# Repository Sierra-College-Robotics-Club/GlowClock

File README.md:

# GlowClock

This is a project from Sierra College Robotics Club, A glow-in-the-dark display, activated by UV LEDs scanning over a glow-in-the-dark surface. It displays messages, the time, and features various patterns and simple games! 

See [The Schematic](GlowClockPCB/Docs/GlowClockSchematicPrint.pdf) and [The Code](code/glowClock.py) to get started working with it.

The GlowClock design evolved from our previous project, the Whiteboard Clock, but with the goals of being more mechanically reliable, while showing a new and unique way of using technology we're all familar with: Glow in the dark materials!

The GlowClock is a collaborative effort by the Robotics Club, featuring PCB design and software by Patrick Leiser, with mechanical design and assembly contributions from many talented club members.

## In the media
We presented the GlowClock at OpenSauce 2025, and were featured in [This Video](https://youtu.be/PQWQQJ_izac?t=115) by Jeff Geerling. We also posted some media on [our instagram](https://www.instagram.com/p/DJci4YWBg5E/)

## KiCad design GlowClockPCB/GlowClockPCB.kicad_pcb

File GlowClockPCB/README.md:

# GlowClock PCB
This PCB was designed to, in addition to supporting the glowclock, be a modular prototyping board for various other projects as well, with all unused GPIO broken out and accessible.

V1.0 boards have been produced and are in active use, V1.1 boards are currently under development.

## Errata
### V1.0
- The second motor-driver board slot (A2) is not fully populated with the required control signals
- The Raspberry Pi 40 pin header (not to be confused with the Pi Pico's socket) has 0.2mm hole spacing instead of the traditional 2.54mm spacing
- The i2c SDA pin for the I2C_LCD connector is connected to GPIO22 instead of GPIO20. This can be resolved by cutting the trace and green-wiring to the Pi Pico pin 26.

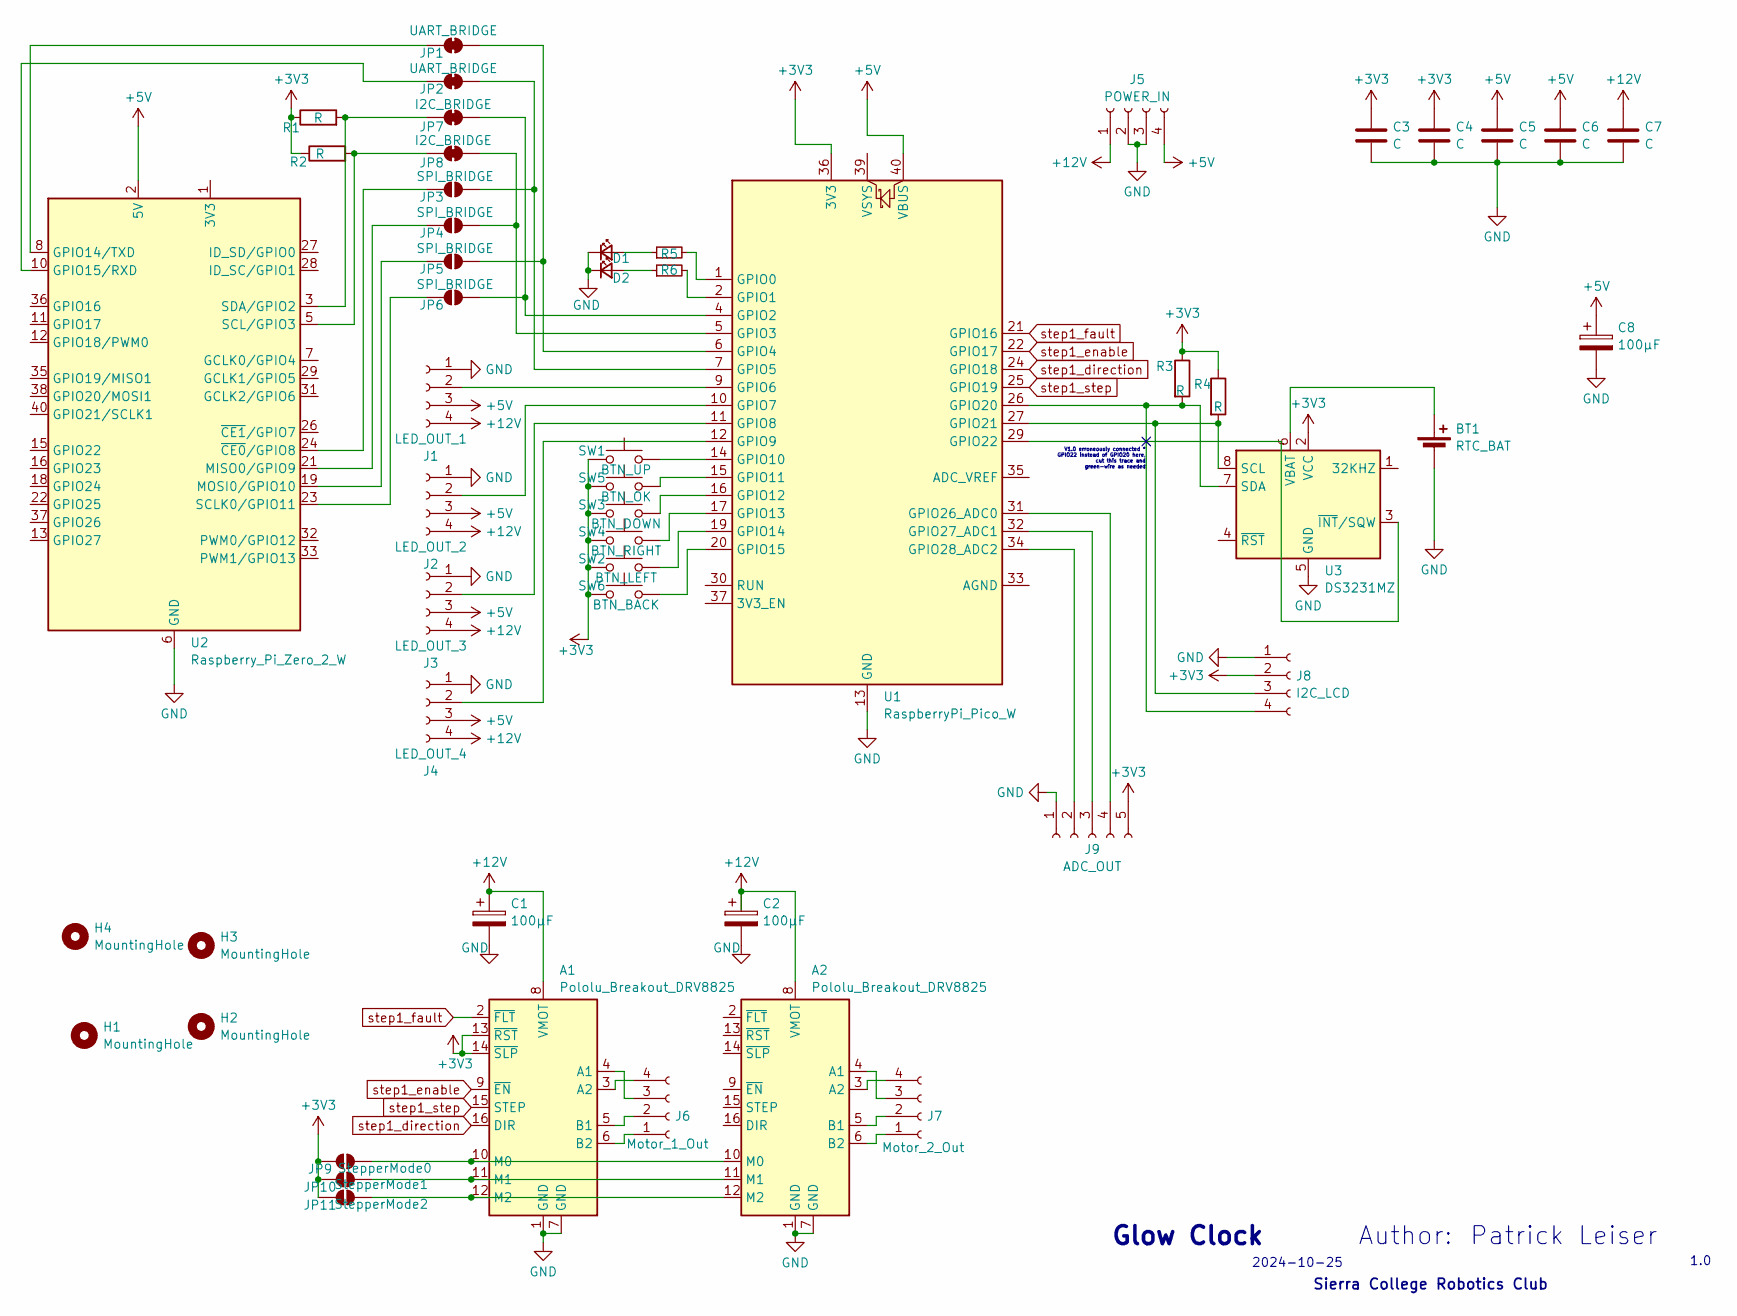
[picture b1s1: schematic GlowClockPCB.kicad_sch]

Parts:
A1, A2: Pololu_Breakout_DRV8825; Pololu_Breakout-16_15.2x20.3mm
BT1: RTC_BAT; BatteryHolder_LINX_BAT-HLD-012-SMT
C1, C2, C8: 100µF; CP_Radial_D10.0mm_P5.00mm
C3, C4, C5, C6, C7: C; C_0603_1608Metric
D1, D2: LED_Small; LED_0603_1608Metric
H1, H2, H3, H4: MountingHole; MountingHole_3.2mm_M3
J1: LED_OUT_1; JST_XH_B4B-XH-A_1x04_P2.50mm_Vertical
J2: LED_OUT_2; JST_XH_B4B-XH-A_1x04_P2.50mm_Vertical
J3: LED_OUT_3; JST_XH_B4B-XH-A_1x04_P2.50mm_Vertical
J4: LED_OUT_4; JST_XH_B4B-XH-A_1x04_P2.50mm_Vertical
J5: POWER_IN; TE_MATE-N-LOK_350211-1_1x04_P5.08mm_Vertical
J6: Motor_1_Out; JST_XH_B4B-XH-A_1x04_P2.50mm_Vertical
J7: Motor_2_Out; JST_XH_B4B-XH-A_1x04_P2.50mm_Vertical
J8: I2C_LCD; PinHeader_1x04_P2.54mm_Vertical
J9: ADC_OUT; JST_XH_B5B-XH-A_1x05_P2.50mm_Vertical
JP1, JP2: UART_BRIDGE; SolderJumper-2_P1.3mm_Bridged_Pad1.0x1.5mm
JP3, JP4, JP5, JP6: SPI_BRIDGE; SolderJumper-2_P1.3mm_Open_Pad1.0x1.5mm
JP7, JP8: I2C_BRIDGE; SolderJumper-2_P1.3mm_Bridged_Pad1.0x1.5mm
JP9: StepperMode0; SolderJumper-2_P1.3mm_Open_Pad1.0x1.5mm
JP10: StepperMode1; SolderJumper-2_P1.3mm_Open_Pad1.0x1.5mm
JP11: StepperMode2; SolderJumper-2_P1.3mm_Open_Pad1.0x1.5mm
R1, R2, R3, R4: R; R_0603_1608Metric
R5, R6: R_Small; R_0603_1608Metric
SW1: BTN_UP; SW_Push_1P1T_NO_6x6mm_H9.5mm
SW2: BTN_LEFT; SW_Push_1P1T_NO_6x6mm_H9.5mm
SW3: BTN_DOWN; SW_Push_1P1T_NO_6x6mm_H9.5mm
SW4: BTN_RIGHT; SW_Push_1P1T_NO_6x6mm_H9.5mm
SW5: BTN_OK; SW_Push_1P1T_NO_6x6mm_H9.5mm
SW6: BTN_BACK; SW_Push_1P1T_NO_6x6mm_H9.5mm
U1: RaspberryPi_Pico_W; RaspberryPi_Pico_Common
U2: Raspberry_Pi_Zero_2_W; PinHeader_2x20_P2.00mm_Vertical
U3: DS3231MZ; SOIC-8_3.9x4.9mm_P1.27mm

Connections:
+3V3: A1.13 (~RST), A1.14 (~SLP), C3.1, C4.1, J8.2, J9.5, JP9.1 (A), JP10.1 (A), JP11.1 (A), R1.1, R2.1, R3.1, R4.1, SW1.1, SW2.1, SW3.1, SW4.1, SW5.1, SW6.1, U1.36 (3V3), U3.2 (VCC)
+5V: C5.1, C6.1, C8.1, J1.3, J2.3, J3.3, J4.3, J5.4, U1.40 (VBUS), U2.2 (5V), U2.4 (5V)
+12V: A1.8 (VMOT), A2.8 (VMOT), C1.1, C2.1, C7.1, J1.4, J2.4, J3.4, J4.4, J5.1
GND: A1.1 (GND), A1.7 (GND), A2.1 (GND), A2.7 (GND), BT1.2 (-), C1.2, C2.2, C3.2, C4.2, C5.2, C6.2, C7.2, C8.2, D1.1 (K), D2.1 (K), J1.1, J2.1, J3.1, J4.1, J5.2, J5.3, J8.1, J9.1, U1.3 (GND), U1.8 (GND), U1.13 (GND), U1.18 (GND), U1.23 (GND), U1.28 (GND), U1.38 (GND), U2.6 (GND), U2.9 (GND), U2.14 (GND), U2.20 (GND), U2.25 (GND), U2.30 (GND), U2.34 (GND), U2.39 (GND), U3.5 (GND)
unnamed: A1.4 (A1), J6.3
unnamed: A1.3 (A2), J6.4
unnamed: A1.5 (B1), J6.2
unnamed: A1.6 (B2), J6.1
unnamed: A1.10 (M0), A2.10 (M0), JP9.2 (B)
unnamed: A1.11 (M1), A2.11 (M1), JP10.2 (B)
unnamed: A1.12 (M2), A2.12 (M2), JP11.2 (B)
unnamed: A2.4 (A1), J7.3
unnamed: A2.3 (A2), J7.4
unnamed: A2.5 (B1), J7.2
unnamed: A2.6 (B2), J7.1
unnamed: BT1.1 (+), U3.6 (VBAT)
unnamed: D1.2 (A), R5.1
unnamed: D2.2 (A), R6.1
unnamed: J1.2, U1.9 (GPIO6)
unnamed: J2.2, U1.10 (GPIO7)
unnamed: J3.2, U1.11 (GPIO8)
unnamed: J4.2, U1.12 (GPIO9)
unnamed: J8.3, R4.2, U1.27 (GPIO21), U3.8 (SCL)
unnamed: J8.4, R3.2, U1.26 (GPIO20), U3.7 (SDA)
unnamed: J9.2, U1.34 (GPIO28_ADC2)
unnamed: J9.3, U1.32 (GPIO27_ADC1)
unnamed: J9.4, U1.31 (GPIO26_ADC0)
unnamed: JP1.1 (A), U2.8 (GPIO14/TXD)
unnamed: JP1.2 (B), JP5.2 (B), U1.6 (GPIO4)
unnamed: JP2.1 (A), U2.10 (GPIO15/RXD)
unnamed: JP2.2 (B), JP3.2 (B), U1.7 (GPIO5)
unnamed: JP3.1 (A), U2.24 (~CE0/GPIO8)
unnamed: JP4.1 (A), U2.21 (MISO0/GPIO9)
unnamed: JP4.2 (B), JP8.2 (B), U1.5 (GPIO3)
unnamed: JP5.1 (A), U2.19 (MOSI0/GPIO10)
unnamed: JP6.1 (A), U2.23 (SCLK0/GPIO11)
unnamed: JP6.2 (B), JP7.2 (B), U1.4 (GPIO2)
unnamed: JP7.1 (A), R1.2, U2.3 (SDA/GPIO2)
unnamed: JP8.1 (A), R2.2, U2.5 (SCL/GPIO3)
unnamed: R5.2, U1.1 (GPIO0)
unnamed: R6.2, U1.2 (GPIO1)
unnamed: SW1.2, U1.14 (GPIO10)
unnamed: SW5.2, U1.15 (GPIO11)
unnamed: SW3.2, U1.16 (GPIO12)
unnamed: SW4.2, U1.17 (GPIO13)
unnamed: SW2.2, U1.19 (GPIO14)
unnamed: SW6.2, U1.20 (GPIO15)
unnamed: U1.29 (GPIO22), U3.3 (~INT/SQW)
unnamed: U2.1 (3V3), U2.17 (3V3)
step1_direction: A1.16 (DIR), U1.24 (GPIO18)
step1_enable: A1.9 (~EN), U1.22 (GPIO17)
step1_fault: A1.2 (~FLT), U1.21 (GPIO16)
step1_step: A1.15 (STEP), U1.25 (GPIO19)

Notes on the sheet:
1.0
Glow Clock
Author:
Patrick Leiser
Sierra College Robotics Club
V1.0 erroneously connected * GPIO22 instead of GPIO20 here, cut this trace and green-wire as needed
2024-10-25

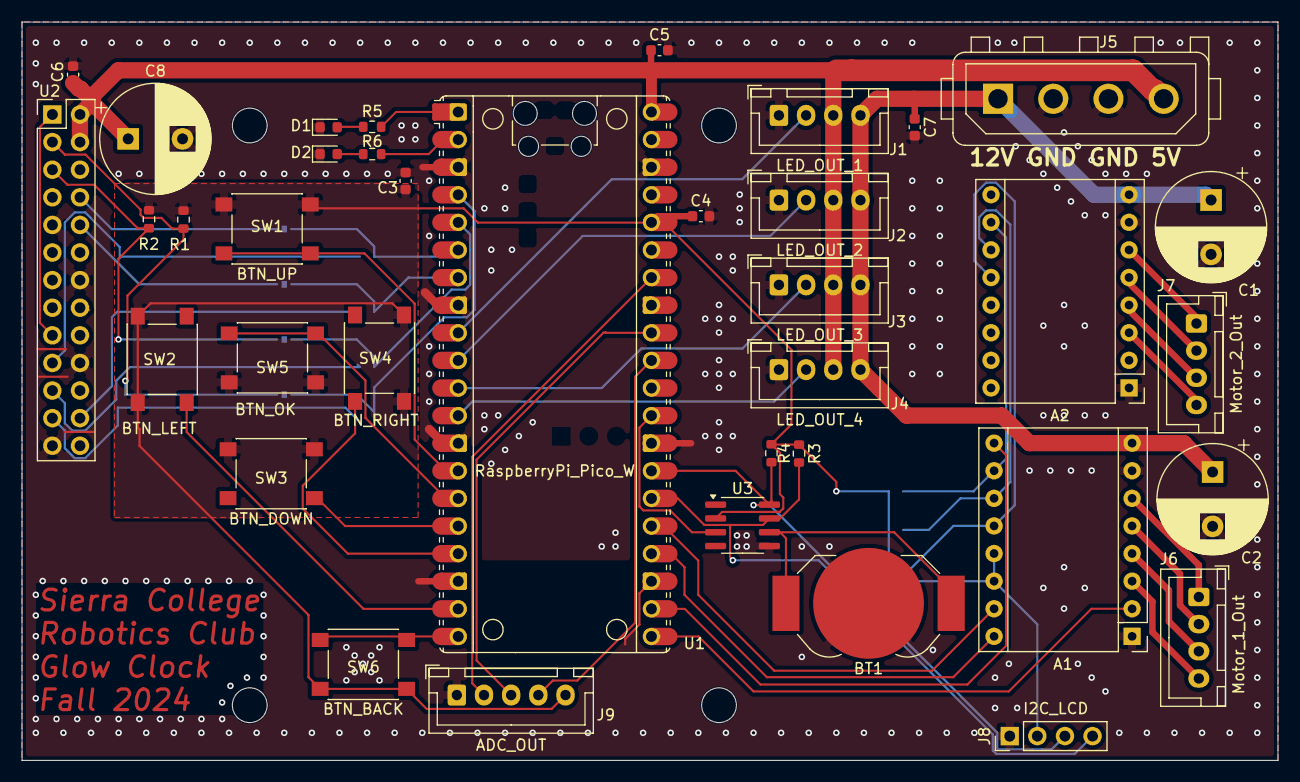
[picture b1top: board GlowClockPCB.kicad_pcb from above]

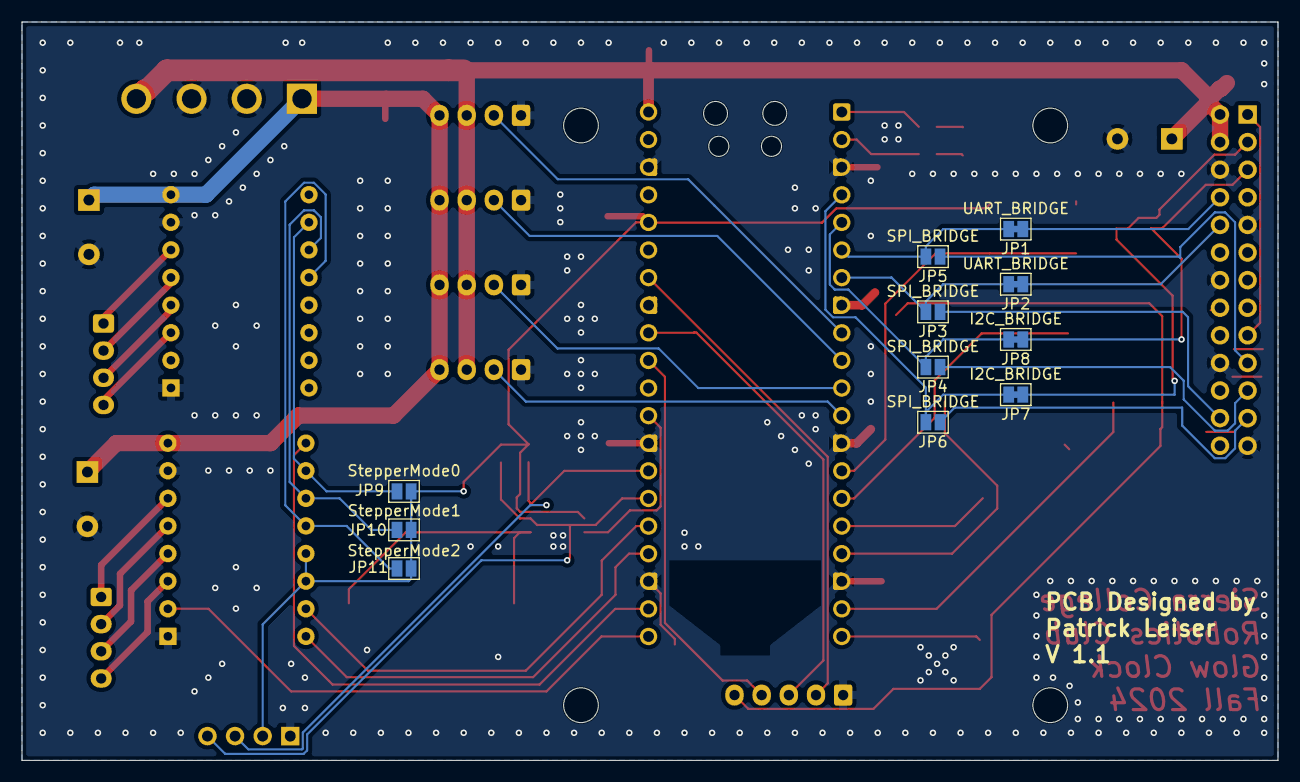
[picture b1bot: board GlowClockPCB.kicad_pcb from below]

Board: 2 copper layers, 115.6 x 67.9 mm, 52 parts (11 on the bottom side), 53 nets.

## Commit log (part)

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2024-09-19 initial commit, most of basic layout and schematic complete
2024-09-19 add output connectors for motor drivers
2024-09-19 thicken high-current traces, and move text from silkscreen to copper layer
2024-10-02 lots of tweaks to design, add display port, mounting holes, decoupling caps, etc
2024-10-02 tweaks to resolve DRC errors
2024-10-25 finalize design for export, add schematic to docs
2024-11-09 add simple demo/test program for driving both uv and rgb neopixels
2024-11-28 simple test of stepper motor, works great
2025-03-07 glowClock.py sucessfully writes messages when manually pushed
2025-03-07 add timing flashes and increase buffer loop speed
2025-04-05 sucessfully writes with hardware, fully functional proof of concept
2025-04-05 reduce usage of magic numbers and other small tweaks
2025-04-11 return 'robotics club' to full brightness
2025-04-11 major code cleanup, add more helper functions, run fast home routine at startup
2025-04-11 use async sleep to improve performance somewhat
2025-04-12 reimplement setPixelColumn to cut delay in half, add timing to track delays, and remove debug logs that added significant delays
2025-04-12 remove unused commented code, comment out profileTiming invocations to further improve performance
2025-04-18 initial implementation switching from circuitPython to MicroPython
2025-04-18 improve stepping smoothness and add debugging count of travel distance
2025-04-25 log skipped steps, lower movement speed to improve reliability, and remove magic number for step timing
2025-04-25 real time clock handling works well! Just need to erase pixels
2025-04-25 commit dependency for rtc
2025-04-25 erasing pixels before updating now works
2025-05-09 display another message each minute
2025-05-10 compress character spacing so 16 characters can be displayed per row
2025-07-10 fix time formatting, add progress bar for sub-minute time indication, add row of usable pixels, add special functions (dots and game)
2025-07-11 add random shapes
2025-07-20 add several more special actions, gradients, and other misc improvements
2025-07-20 add a bunch of 3D models
2025-07-21 update every 30 seconds and change sequential order to be detatched from minutes for day 3 of OpenSauce
2025-08-02 first pass at 2nd led strip handling, attempts to offset other row by 1 pixel for text, non-framebuf displays WIP
2025-08-03 Document pin layout in comments at start of glowClock.py
2025-08-03 Create README.md
    add basic introduction to the project, and links to docs and some media
2025-08-03 Update README.md with another detail
2025-09-14 first pass at adding Hardware Abstraction Layer (HAL) allowing simulation. Simulate Realtime clock to allow existing program to run. Next step is to simulate printing with framebuffer
2025-09-18 add drawBuffer functions to HAL
2025-09-18 Fixed Broken stuff and added Rhombus
2025-10-23 update messages
2025-10-23 add HD mode to rendering, along with improved pixel offset
2025-10-23 fix progressbar and stuck pixel
2025-10-30 Create README.md for the PCB directory, with V1.0 Errata
2025-10-30 typo fix
2025-10-30 fix time display alignment with longer messages
2025-10-30 correct SDA connection for I2C_LCD port
2025-10-30 Replace 40 pin 2.0mm header with 26 pin 2.54mm header
2026-02-10 pcb updates
2026-02-11 fix button brightness and bypass stuck up-button
2026-02-27 implement simulator's ability to print the pixels, just uncomment #HARDWARE = 'PICO_SIM' in HAL.py
2026-04-28 Enable configurable display duration, add display of date and weekday, update messages, and update RTC time
2026-04-28 Update PCB to Kicad 10
2026-06-19 update schematic to annotate v1 pcb errata, add ibom and svg schematic
2026-06-21 update stepperTest.py from circuitpython to micropython
